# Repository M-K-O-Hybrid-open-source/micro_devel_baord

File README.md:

# micro_devel_baord
development board for motor drives, specifically for isolated drives

# 3D_view

# PCB layout

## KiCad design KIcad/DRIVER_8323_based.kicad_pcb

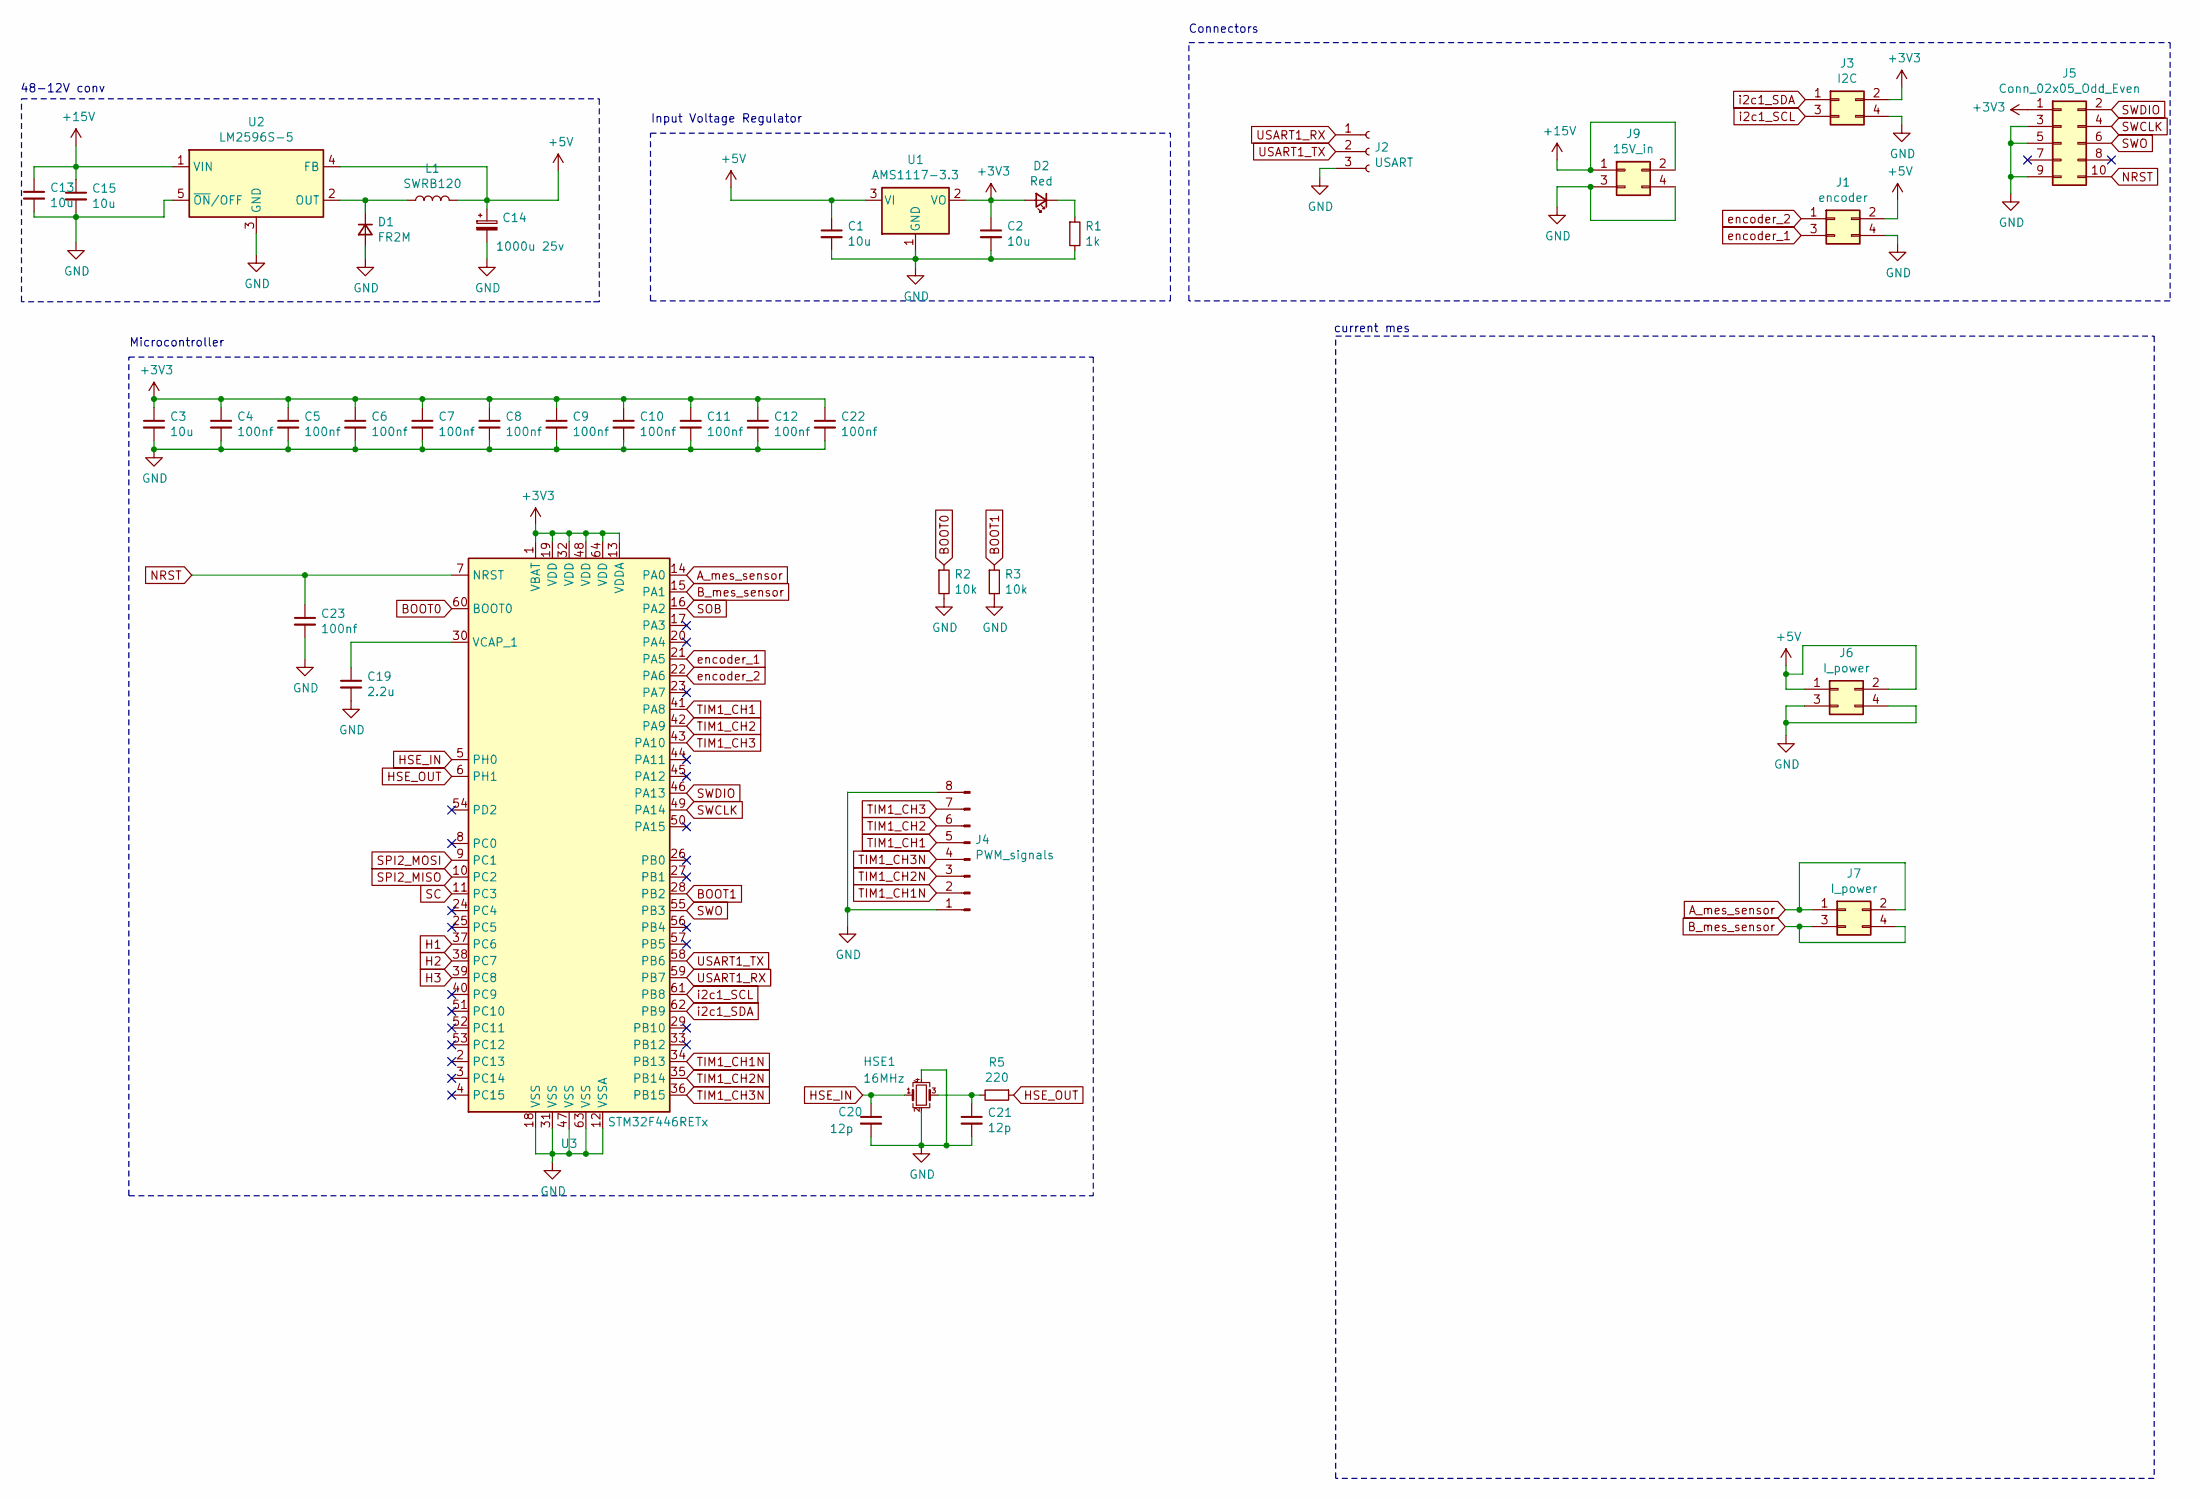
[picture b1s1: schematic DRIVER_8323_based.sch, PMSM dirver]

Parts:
C1, C2, C13, C15: 10u; C_0805_2012Metric
C3: 10u; C_0603_1608Metric
C4, C5, C6, C7, C8, C9, C10, C11, C12, C22, C23: 100nf; C_0402_1005Metric
C14: 1000u 25v; CP_Elec_10x10
C19: 2.2u; C_0603_1608Metric
C20, C21: 12p; C_0402_1005Metric
D1: FR2M; D_SMB
D2: Red; LED_0603_1608Metric
HSE1: 16MHz; Crystal_SMD_3225-4Pin_3.2x2.5mm
J1: encoder; PinHeader_2x02_P2.54mm_Horizontal
J2: USART; PinHeader_1x03_P2.54mm_Vertical
J3: I2C; PinHeader_2x02_P2.54mm_Horizontal
J4: PWM_signals; PinHeader_1x08_P1.27mm_Vertical
J5: Conn_02x05_Odd_Even; PinHeader_2x05_P2.54mm_Vertical
J6, J7: I_power; PinSocket_2x02_P2.54mm_Vertical
J9: 15V_in; PinHeader_2x02_P2.54mm_Vertical
L1: SWRB120; L_12x12mm_H4.5mm
R1: 1k; R_0603_1608Metric
R2, R3: 10k; R_0805_2012Metric
R5: 220; R_0603_1608Metric
U1: AMS1117-3.3; SOT-223-3_TabPin2
U2: LM2596S-5; TO-263-5_TabPin3
U3: STM32F446RETx; LQFP-64_10x10mm_P0.5mm

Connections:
+3V3: C2.1, C3.1, C4.1, C5.1, C6.1, C7.1, C8.1, C9.1, C10.1, C11.1, C12.1, C22.1, D2.2 (A), J3.2, J5.1, U1.2 (VO), U3.1 (VBAT), U3.13 (VDDA), U3.19 (VDD), U3.32 (VDD), U3.48 (VDD), U3.64 (VDD)
+5V: C1.1, C14.1, J1.2, J6.1, J6.2, L1.2, U1.3 (VI), U2.4 (FB)
+15V: C13.1, C15.1, J9.1, J9.2, U2.1 (VIN)
A_mes_sensor: J7.1, J7.2, U3.14 (PA0)
BOOT0: R2.1, U3.60 (BOOT0)
BOOT1: R3.1, U3.28 (PB2)
B_mes_sensor: J7.3, J7.4, U3.15 (PA1)
GND: C1.2, C2.2, C3.2, C4.2, C5.2, C6.2, C7.2, C8.2, C9.2, C10.2, C11.2, C12.2, C13.2, C14.2, C15.2, C19.2, C20.2, C21.2, C22.2, C23.2, D1.2 (A), HSE1.2, HSE1.4, J1.4, J2.3, J3.4, J4.1, J4.8, J5.3, J5.5, J5.9, J6.3, J6.4, J9.3, J9.4, R1.2, R2.2, R3.2, U1.1 (GND), U2.3 (GND), U2.5 (~ON~/OFF), U3.12 (VSSA), U3.18 (VSS), U3.31 (VSS), U3.47 (VSS), U3.63 (VSS)
H1: U3.37 (PC6)
H2: U3.38 (PC7)
H3: U3.39 (PC8)
HSE_IN: C20.1, HSE1.1, U3.5 (PH0)
HSE_OUT: R5.1, U3.6 (PH1)
NRST: C23.1, J5.10, U3.7 (NRST)
unnamed: C19.1, U3.30 (VCAP_1)
unnamed: C21.1, HSE1.3, R5.2
unnamed: D1.1 (K), L1.1, U2.2 (OUT)
unnamed: D2.1 (K), R1.1
SC: U3.11 (PC3)
SOB: U3.16 (PA2)
SPI2_MISO: U3.10 (PC2)
SPI2_MOSI: U3.9 (PC1)
SWCLK: J5.4, U3.49 (PA14)
SWDIO: J5.2, U3.46 (PA13)
SWO: J5.6, U3.55 (PB3)
TIM1_CH1: J4.5, U3.41 (PA8)
TIM1_CH1N: J4.2, U3.34 (PB13)
TIM1_CH2: J4.6, U3.42 (PA9)
TIM1_CH2N: J4.3, U3.35 (PB14)
TIM1_CH3: J4.7, U3.43 (PA10)
TIM1_CH3N: J4.4, U3.36 (PB15)
USART1_RX: J2.1, U3.59 (PB7)
USART1_TX: J2.2, U3.58 (PB6)
encoder_1: J1.3, U3.21 (PA5)
encoder_2: J1.1, U3.22 (PA6)
i2c1_SCL: J3.3, U3.61 (PB8)
i2c1_SDA: J3.1, U3.62 (PB9)

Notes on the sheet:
Input Voltage Regulator
Microcontroller
Connectors
48-12V conv
current mes

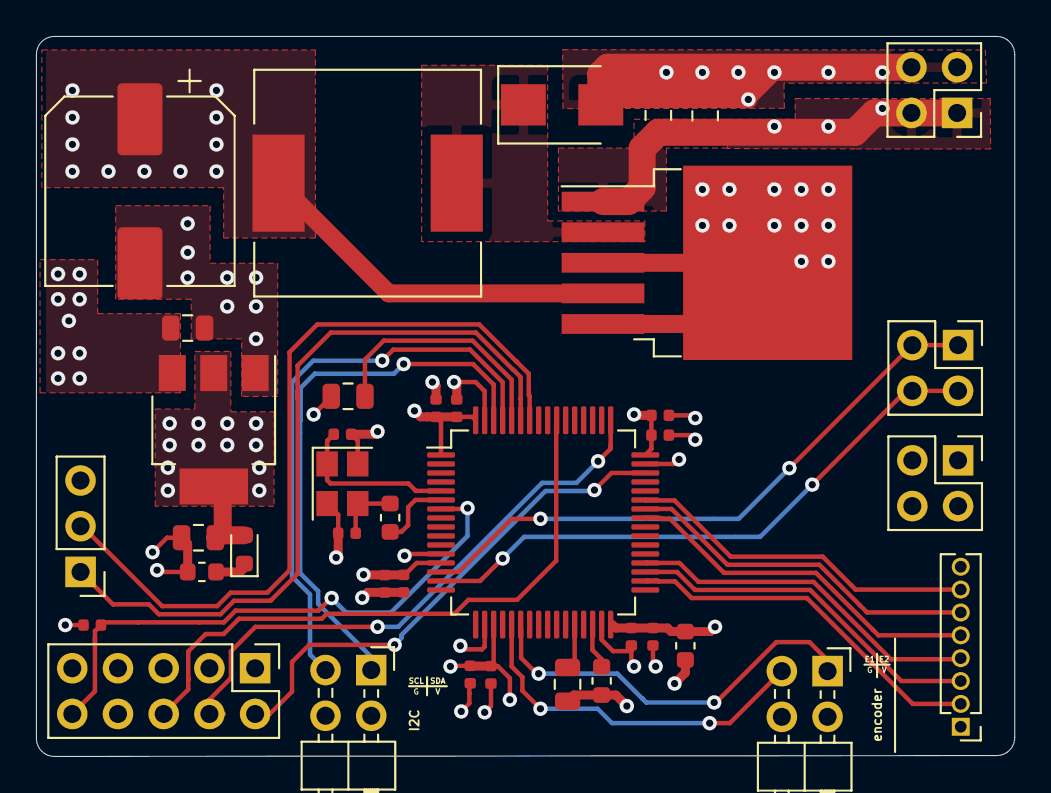
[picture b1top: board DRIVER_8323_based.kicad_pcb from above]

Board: 4 copper layers, 54.3 x 40.0 mm, 39 parts (0 on the bottom side), 30 nets.
